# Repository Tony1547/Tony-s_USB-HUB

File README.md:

# Tony's_USB-HUB

a derived project from my laptop stand, something more portable

CAD: https://cad.onshape.com/documents/6a81ff5d2388544458bf9e52/w/846476873ab57c03fea54f85/e/cf2f55c22f1db6e96002cb24

BOM: https://docs.google.com/spreadsheets/d/1JnSKWipZPriSM-YKTiYsPfFD8vnBWgR8qAoonC7MyM4/edit?usp=sharing

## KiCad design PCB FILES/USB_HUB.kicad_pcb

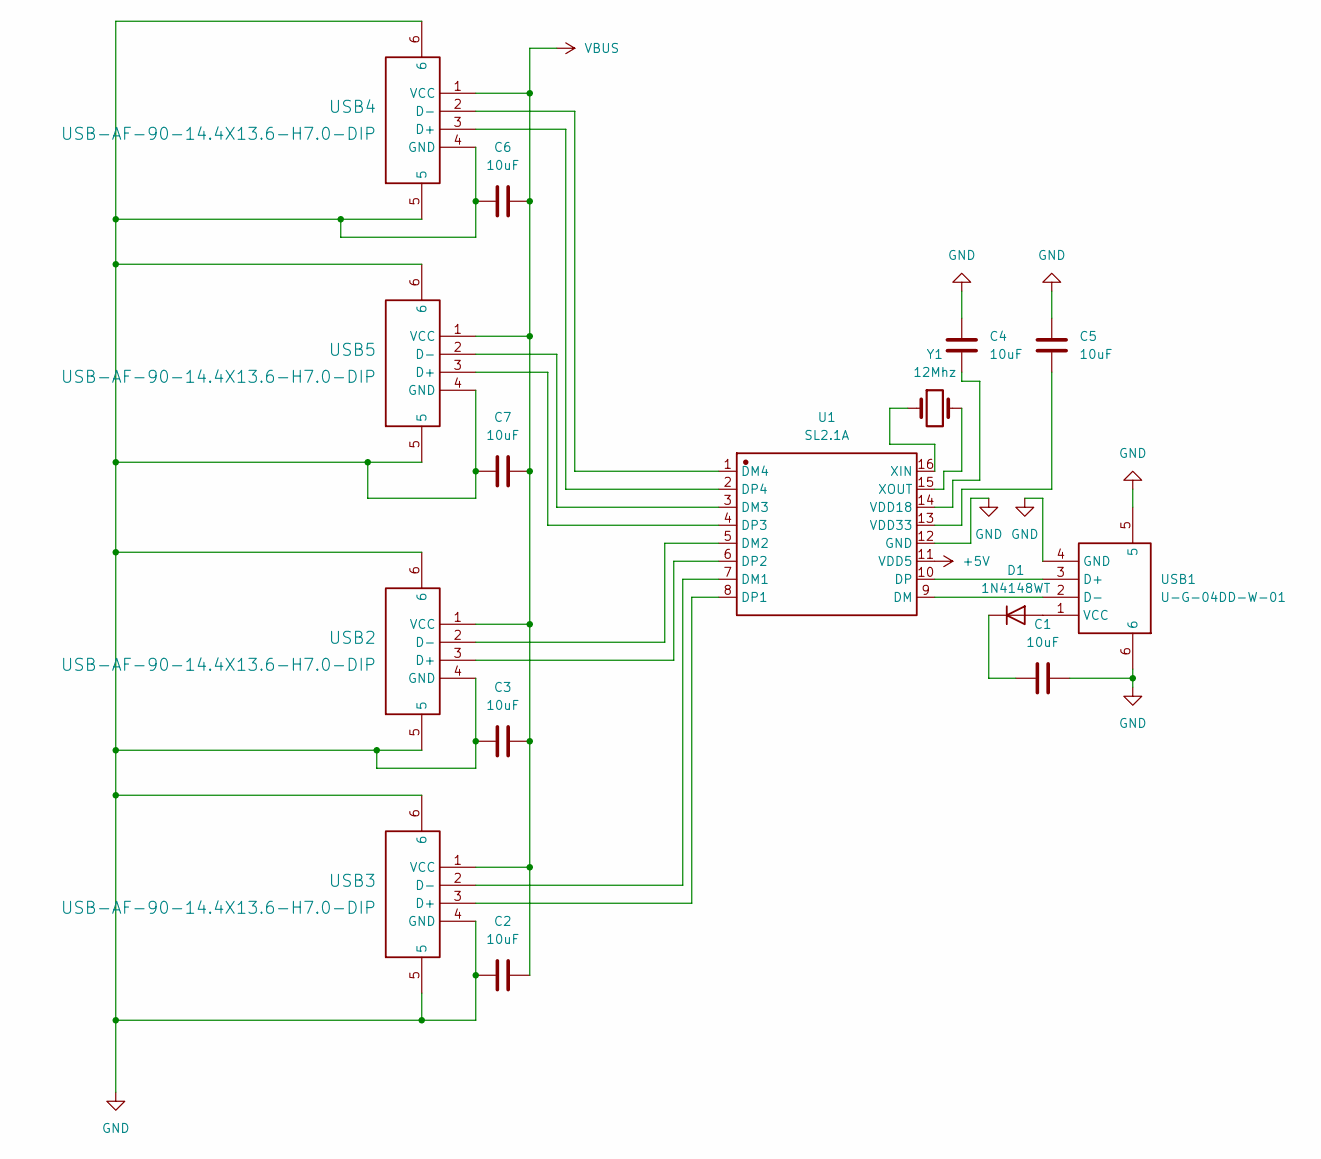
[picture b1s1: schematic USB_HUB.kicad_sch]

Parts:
C1, C2, C3, C4, C5, C6, C7: 10uF; C_0201_0603Metric_Pad0.64x0.40mm_HandSolder
D1: 1N4148WT; D_SOD-523
U1: SL2.1A; SOP-16_L10.0-W3.9-P1.27-LS6.0-BL; Manufacturer Part SL2.1A
USB1: U-G-04DD-W-01; USB-A-TH_U-G-04WD-W-01; Manufacturer Part U-G-O4DD-W-1
USB2, USB3, USB4, USB5: USB-AF-90-14.4X13.6-H7.0-DIP; USB-A-TH_C46407; Manufacturer Part 903-131A1011D10100
Y1: 12Mhz; Crystal_SMD_0603-2Pin_6.0x3.5mm_HandSoldering

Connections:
+5V: U1.11 (VDD5)
GND: C1.2, C2.2, C3.2, C4.2, C5.2, C6.2, C7.2, U1.12 (GND), USB1.4 (GND), USB1.5, USB1.6, USB2.4 (GND), USB2.5, USB2.6, USB3.4 (GND), USB3.5, USB3.6, USB4.4 (GND), USB4.5, USB4.6, USB5.4 (GND), USB5.5, USB5.6
unnamed: D1.2 (A), USB1.1 (VCC)
unnamed: C1.1, D1.1 (K)
unnamed: U1.7 (DM1), USB3.2 (D-)
unnamed: U1.5 (DM2), USB2.2 (D-)
unnamed: U1.3 (DM3), USB5.2 (D-)
unnamed: U1.1 (DM4), USB4.2 (D-)
unnamed: U1.9 (DM), USB1.2 (D-)
unnamed: U1.8 (DP1), USB3.3 (D+)
unnamed: U1.6 (DP2), USB2.3 (D+)
unnamed: U1.4 (DP3), USB5.3 (D+)
unnamed: U1.2 (DP4), USB4.3 (D+)
unnamed: U1.10 (DP), USB1.3 (D+)
unnamed: C4.1, U1.14 (VDD18)
unnamed: C5.1, U1.13 (VDD33)
unnamed: U1.16 (XIN), Y1.1
unnamed: U1.15 (XOUT), Y1.2
VBUS: C2.1, C3.1, C6.1, C7.1, USB2.1 (VCC), USB3.1 (VCC), USB4.1 (VCC), USB5.1 (VCC)

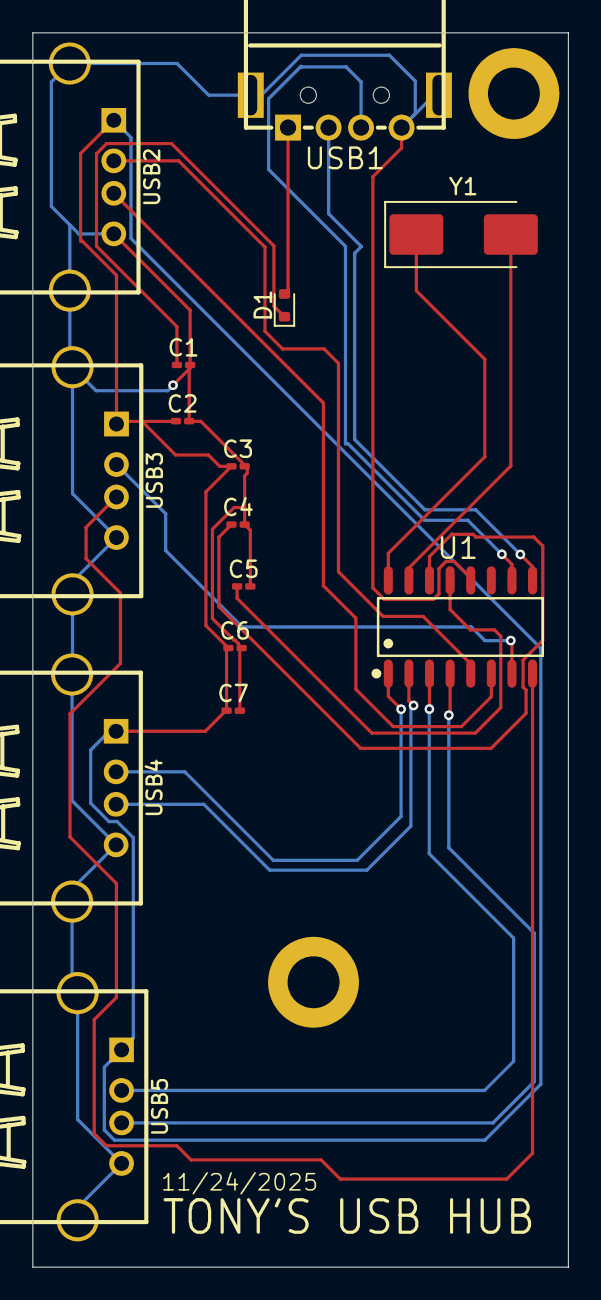
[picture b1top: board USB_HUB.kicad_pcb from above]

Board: 2 copper layers, 33.0 x 76.1 mm, 15 parts (0 on the bottom side), 18 nets.

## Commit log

2025-11-27 file
2025-11-27 files
2025-11-27 gerb
